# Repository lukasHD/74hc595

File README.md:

# 74hc595 Library

Simple Library for my Shift Register Board.

## Impressions

## Usage

Connect `Serin`, `serial clock` and `register clock` to GPIO pins on the Raspberry Pi.
Use the GPIO numbers that are GPIOXX and not the pin numbers.

Connect `CLR` Pin to `3.3V` to enable storage in the serin-serout chain (we have a pull-down instead of a pull-up).
Connect `CLR` to a GPIO pin if you need to clear at some point in the program.

Connect `OE` to a GPIO if you need to disable the outputs at some point in the program. 

## Open Issues

### Hardware

* LEDs are quite bright --> Increase Resistors to 100 Ohm
* Pull-DOWN resistor on clear/reset should be an Pull-UP resistor
* can we squeeze the leyout so that we are one row smaller on a prototyping board

### Software

* Expand to multiple Shiftregisters
* Fix the Linting 
* Tune the delays so we don't waste time sleeping
* Add `OE` and `CLR` support in the library

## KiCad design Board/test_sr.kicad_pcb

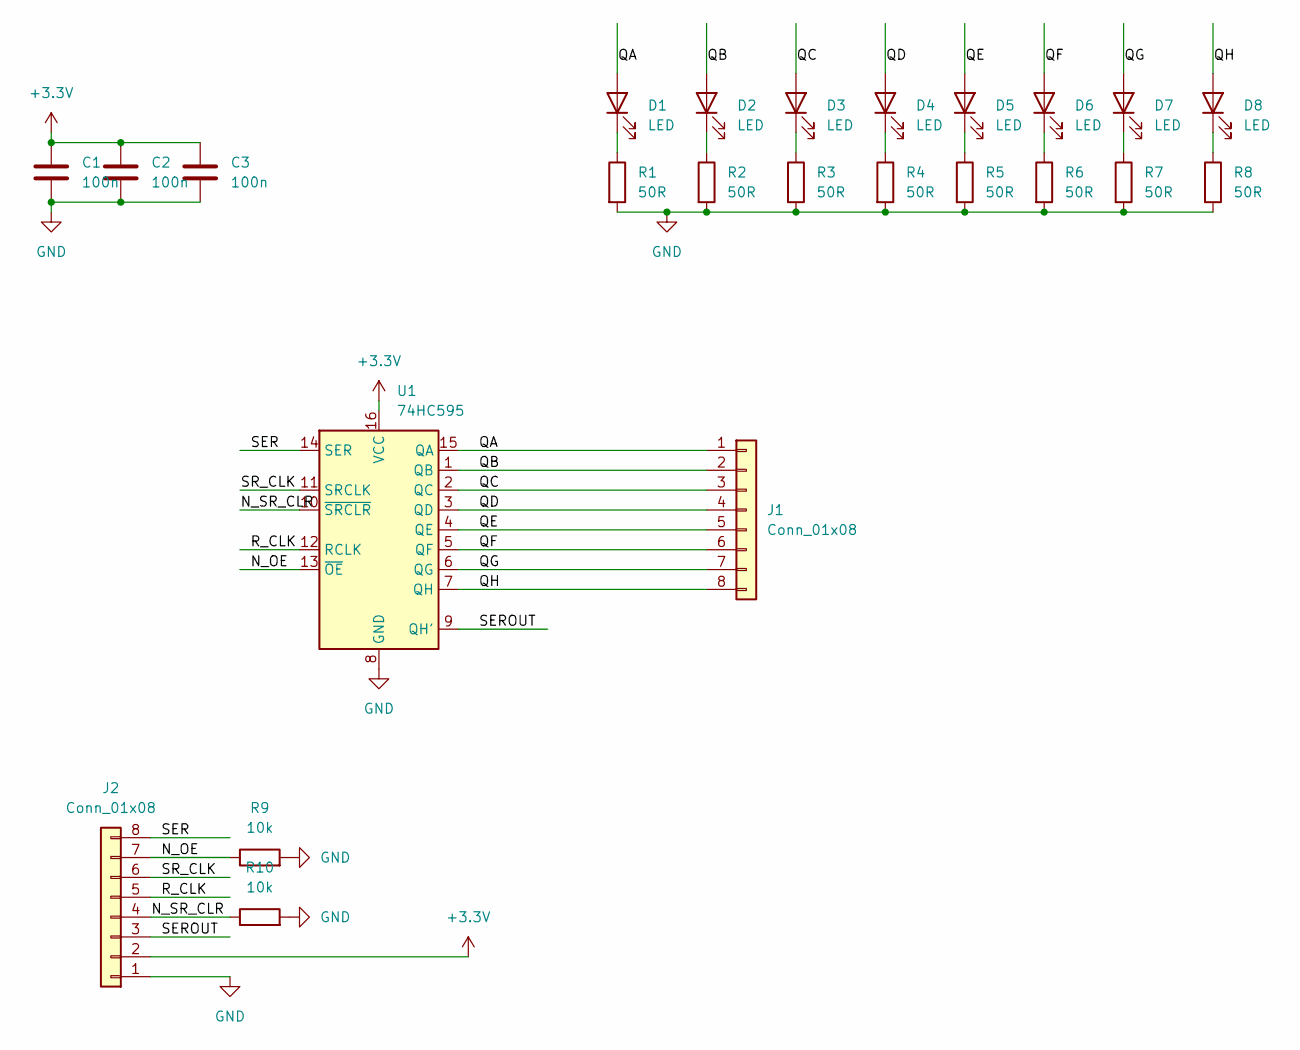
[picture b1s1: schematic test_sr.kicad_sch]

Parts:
C1, C2, C3: 100n; C_0603_1608Metric; LCSC C14663
D1, D2, D3, D4, D5, D6, D7, D8: LED; LED_0603_1608Metric; LCSC C72041
J1, J2: Conn_01x08; PinHeader_1x08_P2.54mm_Vertical
R1, R2, R3, R4, R5, R6, R7, R8: 50R; R_0603_1608Metric; LCSC C23197
R9, R10: 10k; R_0603_1608Metric; LCSC C25804
U1: 74HC595; SOIC-16_4.55x10.3mm_P1.27mm; LCSC C5947

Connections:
+3.3V: C1.1, C2.1, C3.1, J2.2, U1.16 (VCC)
/N_OE: J2.7, R9.1, U1.13 (~OE)
/N_SR_CLR: J2.4, R10.1, U1.10 (~SRCLR)
/QA: D1.2 (A), J1.1, U1.15 (QA)
/QB: D2.2 (A), J1.2, U1.1 (QB)
/QC: D3.2 (A), J1.3, U1.2 (QC)
/QD: D4.2 (A), J1.4, U1.3 (QD)
/QE: D5.2 (A), J1.5, U1.4 (QE)
/QF: D6.2 (A), J1.6, U1.5 (QF)
/QG: D7.2 (A), J1.7, U1.6 (QG)
/QH: D8.2 (A), J1.8, U1.7 (QH)
/R_CLK: J2.5, U1.12 (RCLK)
/SER: J2.8, U1.14 (SER)
/SEROUT: J2.3, U1.9 (QH')
/SR_CLK: J2.6, U1.11 (SRCLK)
GND: C1.2, C2.2, C3.2, J2.1, R1.2, R2.2, R3.2, R4.2, R5.2, R6.2, R7.2, R8.2, R9.2, R10.2, U1.8 (GND)
unnamed: D1.1 (K), R1.1
unnamed: D2.1 (K), R2.1
unnamed: D3.1 (K), R3.1
unnamed: D4.1 (K), R4.1
unnamed: D5.1 (K), R5.1
unnamed: D6.1 (K), R6.1
unnamed: D7.1 (K), R7.1
unnamed: D8.1 (K), R8.1

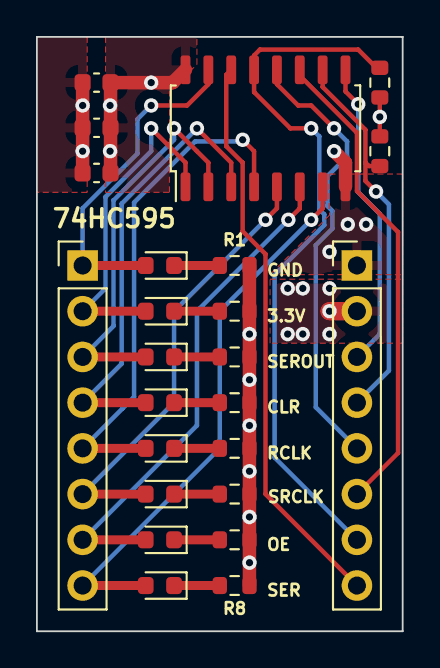
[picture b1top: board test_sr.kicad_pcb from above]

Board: 4 copper layers, 20.3 x 33.0 mm, 24 parts (0 on the bottom side), 24 nets.

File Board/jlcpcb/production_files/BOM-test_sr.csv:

Comment,Designator,Footprint,LCSC
100n,"C1,C2,C3",C_0603_1608Metric,C14663
50R,"R1,R2,R3,R4,R5,R6,R7,R8",R_0603_1608Metric,C23197
10k,"R10,R9",R_0603_1608Metric,C25804
74HC595,U1,SOIC-16_4.55x10.3mm_P1.27mm,C5947
LED,"D1,D2,D3,D4,D5,D6,D7,D8",LED_0603_1608Metric,C72041
Conn_01x08,J2,PinHeader_1x08_P2.54mm_Vertical,
Conn_01x08,J1,PinHeader_1x08_P2.54mm_Vertical,

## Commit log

2023-10-25 erste version
2023-10-25 Create LICENSE
2023-10-25 add the Board
2023-10-25 some linting
2023-10-26 refactor
2023-10-26 more refactor
2023-10-26 readme adn disable workflow
2023-10-26 more docs
2023-11-01 fix timing
2023-11-01 faster demo
2023-11-10 more testing
2023-11-10 tested with 2 SRs
2024-02-07 Lukas hd patch 1 (#1)
    * Add files via upload
    * Update README.md
